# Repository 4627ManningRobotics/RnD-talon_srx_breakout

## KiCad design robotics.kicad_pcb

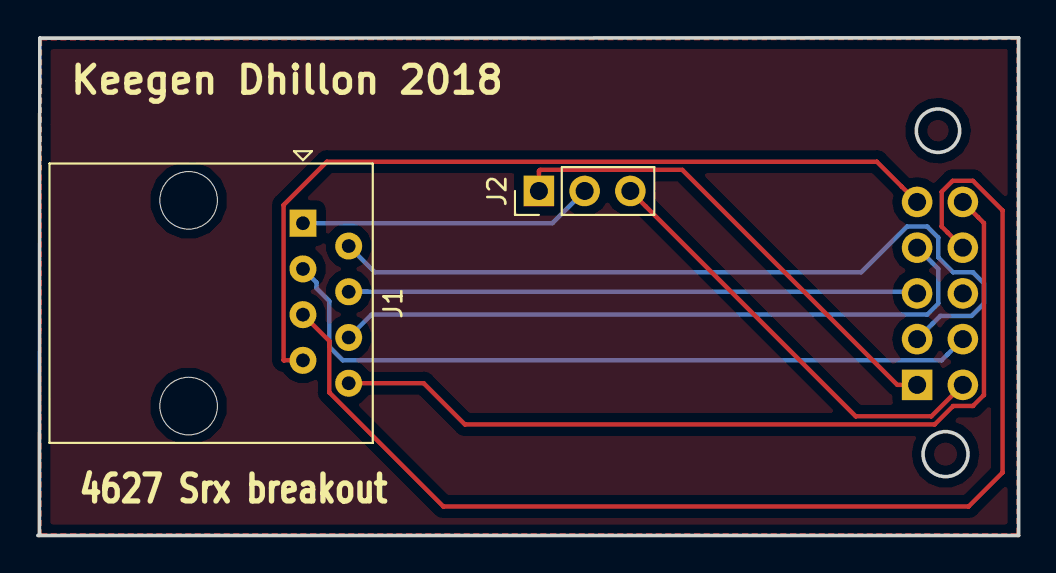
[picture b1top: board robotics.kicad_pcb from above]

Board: 2 copper layers, 54.5 x 27.6 mm, 3 parts (1 on the bottom side), 10 nets.

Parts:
J1: RJ45; RJ45_Amphenol_54602-x08_Horizontal
J2: Conn_01x03; PinHeader_1x03_P2.54mm_Vertical
J3: Conn_02x05_Odd_Even; PinHeader_2x05_P2.54mm_Vertical

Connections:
unnamed: J1.1, J2.2
unnamed: J1.2, J3.3
unnamed: J1.3, J3.4
unnamed: J1.4, J3.5
unnamed: J1.5, J3.8
unnamed: J1.6, J3.7
unnamed: J1.7, J3.9
unnamed: J1.8, J3.10
unnamed: J2.1, J3.1
unnamed: J2.3, J3.2

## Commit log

2019-01-31 inital import of talon breakout board
2019-01-31 changed j1 to j3
